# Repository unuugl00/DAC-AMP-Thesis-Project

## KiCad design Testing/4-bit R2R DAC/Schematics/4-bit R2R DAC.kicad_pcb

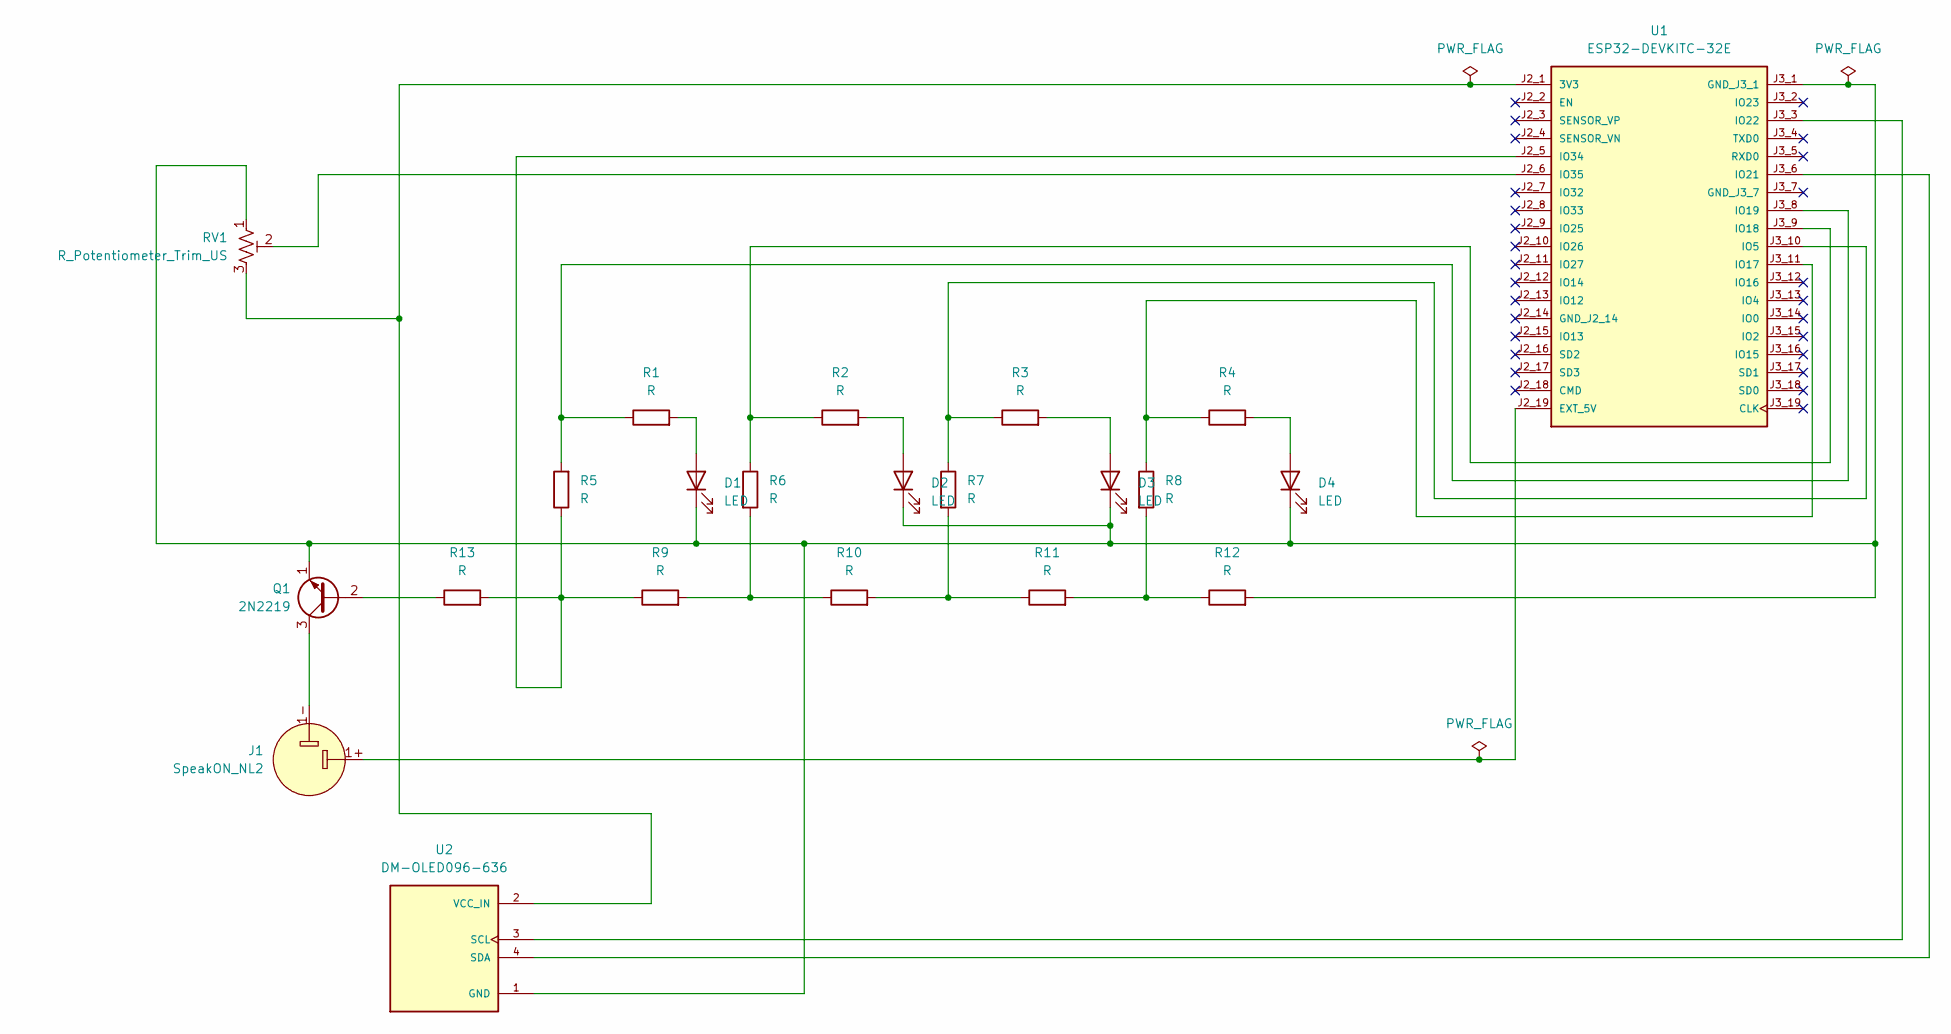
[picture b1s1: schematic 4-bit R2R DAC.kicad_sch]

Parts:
D1, D2, D3, D4: LED; LED_D3.0mm_Clear
J1: SpeakON_NL2; Jack_speakON_Neutrik_NL2MDXX-V_Vertical
Q1: 2N2219; TO-39-3
R1, R2, R3, R4, R5, R6, R7, R8, R9, R10, R11, R12, R13: R; R_Axial_DIN0204_L3.6mm_D1.6mm_P5.08mm_Horizontal
RV1: R_Potentiometer_Trim_US; Potentiometer_Bourns_3296W_Vertical
U1: ESP32-DEVKITC-32E; MODULE_ESP32-DEVKITC-32E; PARTREV 1.4
U2: DM-OLED096-636; MODULE_DM-OLED096-636; PARTREV 2018-09-10

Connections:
unnamed: D1.2 (A), R1.2
unnamed: D1.1 (K), D2.1 (K), D3.1 (K), D4.1 (K), Q1.1 (E), R12.2, RV1.1, U1.J3_1 (GND_J3_1), U2.1 (GND)
unnamed: D2.2 (A), R2.2
unnamed: D3.2 (A), R3.2
unnamed: D4.2 (A), R4.2
unnamed: Q1.2 (B), R13.1
unnamed: J1.1-, Q1.3 (C)
unnamed: R6.2, R9.2, R10.1
unnamed: R7.2, R10.2, R11.1
unnamed: R8.2, R11.2, R12.1
unnamed: RV1.3, U1.J2_1 (3V3), U2.2 (VCC_IN)
unnamed: J1.1+, U1.J2_19 (EXT_5V)
unnamed: R3.1, R7.1, U1.J3_10 (IO5)
unnamed: R4.1, R8.1, U1.J3_11 (IO17)
unnamed: R2.1, R6.1, U1.J3_9 (IO18)
unnamed: R1.1, R5.2, U1.J3_8 (IO19)
unnamed: U1.J3_6 (IO21), U2.4 (SDA)
unnamed: U1.J3_3 (IO22), U2.3 (SCL)
unnamed: R5.1, R9.1, R13.2, U1.J2_5 (IO34)
unnamed: RV1.2, U1.J2_6 (IO35)

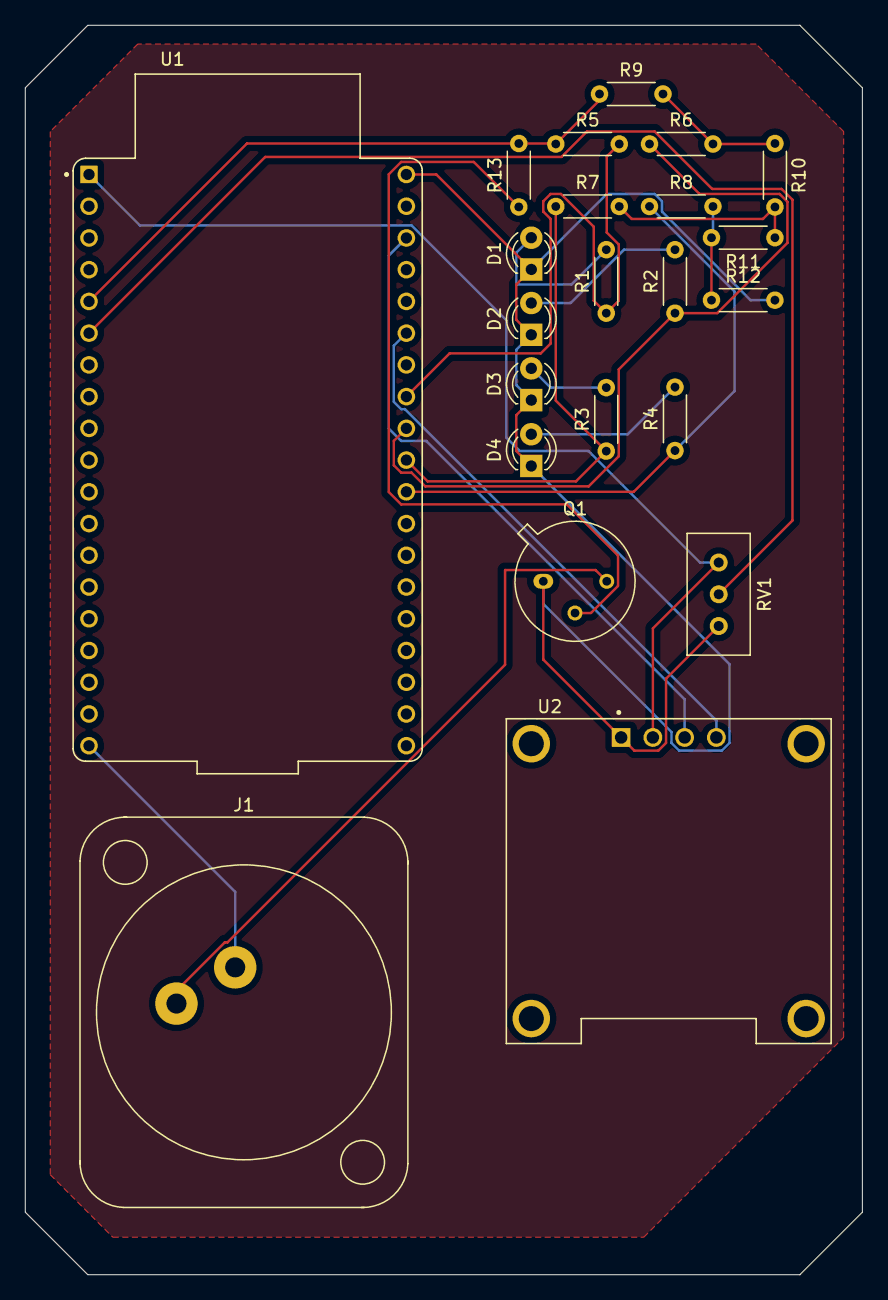
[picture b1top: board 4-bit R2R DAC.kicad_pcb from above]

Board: 2 copper layers, 67.0 x 100.0 mm, 22 parts (0 on the bottom side), 20 nets.

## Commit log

2025-10-23 Testing folder fix
2025-10-23 Add MIT License to the project
2025-10-23 .gitignore
2025-10-23 Update .gitignore file
2025-10-23 Schematics Update
